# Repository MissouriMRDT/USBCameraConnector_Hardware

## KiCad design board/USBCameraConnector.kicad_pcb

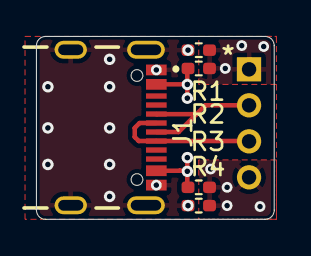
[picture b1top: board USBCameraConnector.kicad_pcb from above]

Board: 2 copper layers, 13.2 x 10.2 mm, 6 parts (0 on the bottom side), 6 nets.

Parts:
J1: USB4105-GF-A; GCT_USB4105-GF-A
J7: Conn_01x04_Pin; PinHeader_1x04_P2.00mm_Vertical
R1, R2, R3, R4: R_Small; R_0402_1005Metric_Pad0.72x0.64mm_HandSolder

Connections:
DN: J1.A7 (DN1), J1.B7 (DN2), J7.2
DP: J1.A6 (DP1), J1.B6 (DP2), J7.3
GND: J1.A1_B12 (GND), J1.B1_A12 (GND__1), J1.SH1 (SHELL_GND), J1.SH2 (SHELL_GND__1), J1.SH3 (SHELL_GND__2), J1.SH4 (SHELL_GND__3), R1.2, R4.2
unnamed: J7.1, R1.1, R2.2
unnamed: J7.4, R3.2, R4.1
VBUS: J1.A4_B9 (VBUS), J1.B4_A9 (VBUS__1), R2.1, R3.1

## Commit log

2025-10-19 Done
2025-11-12 Add github workflow
2025-11-12 Make not castellated holes
2025-11-12 Via stitch planes better
2025-11-12 Better GND vias
2026-03-02 Random commit to test webhook
